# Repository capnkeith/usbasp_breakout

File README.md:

# usbasp_breakout
A breakout board to aid in connecting and disconnecting a USBASP or similar from a breadboard rapidly. Features an RJ45, 10x1 header, 5x2 header, and 3x2 header. Fits most simple ISP programmers

This is a kikad project. 

Pinouts:

10x1 header 

	1 - VCC
	2 - GND
	3 - MOSI
	4 - VCC
	5 - RESET
	6 - SCK
	7 - MISO 
	8 - GND
 
5x2 header

	1 - MISO
	2 - VCC
	3 - NC
	4 - GND
	5 - RESET
	6 - GND
	7 - SCK
	8 - GND
	9 - MISO
	10 - GND 
 
3x2 Header

	1 - MISO
	2 - VCC
	3 - SCK
	4 - MOSI
	5 - RESET
	6 - GND
 
RJ45 Connector

	1 - VCC
	2 - NC
	3 - MOSI
	4 - NC
	5 - REST
	6 - SCK
	7 - MISO
	8 - GND

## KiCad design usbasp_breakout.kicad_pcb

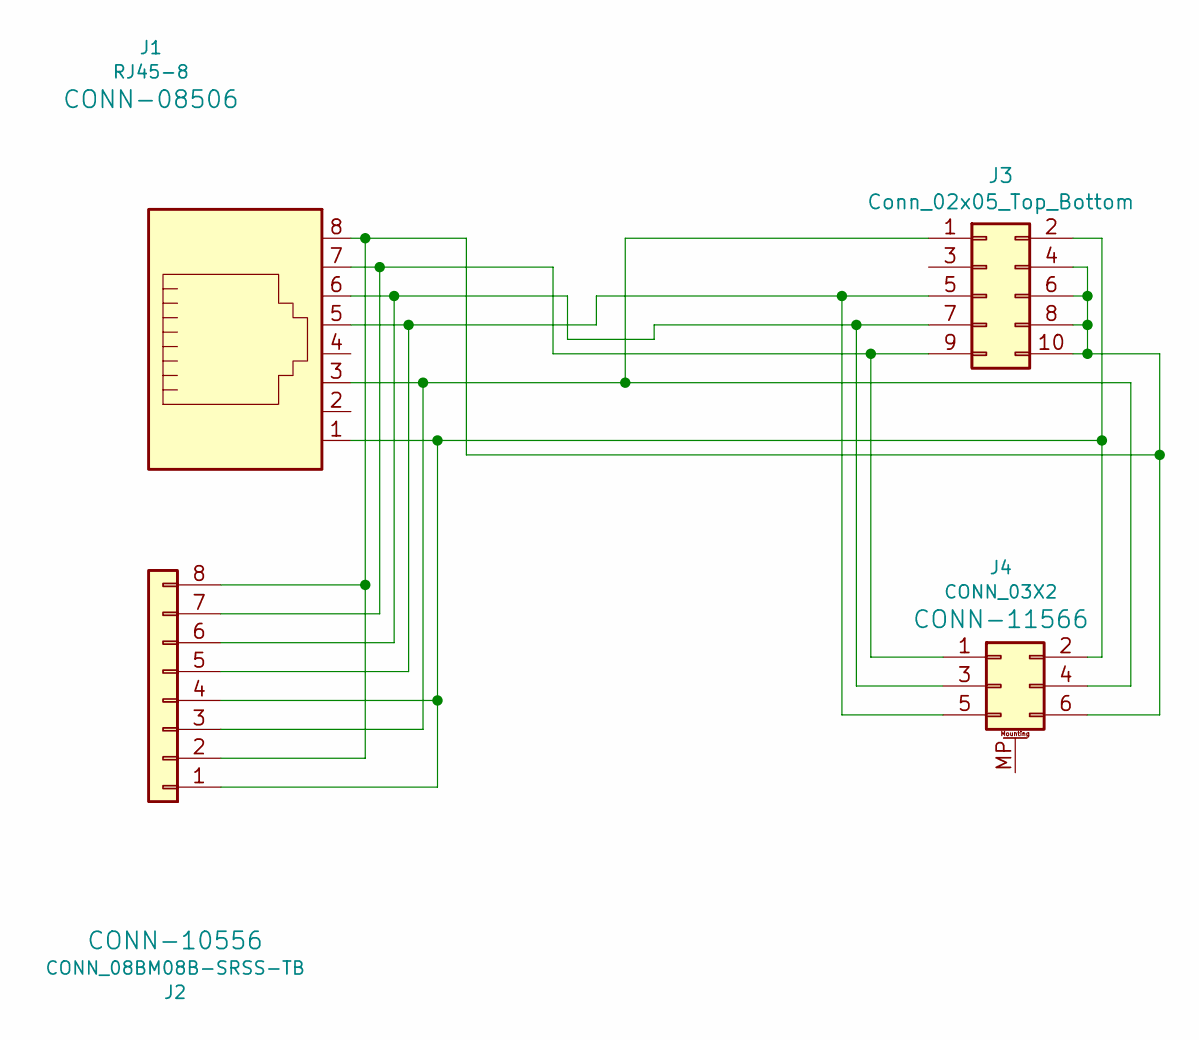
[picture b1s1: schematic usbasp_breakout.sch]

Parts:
J1: RJ45-8; RJ45_Amphenol_54602-x08_Horizontal
J2: CONN_08BM08B-SRSS-TB; PinHeader_1x08_P2.54mm_Vertical
J3: Conn_02x05_Top_Bottom; PinSocket_2x05_P2.54mm_Vertical
J4: CONN_03X2; PinSocket_2x03_P2.54mm_Vertical

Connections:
unnamed: J1.1, J2.1, J2.4, J3.2, J4.2
unnamed: J1.3, J2.3, J3.1, J4.4
unnamed: J1.5, J2.5, J3.5, J4.5
unnamed: J1.6, J2.6, J3.7, J4.3
unnamed: J1.7, J2.7, J3.9, J4.1
unnamed: J1.8, J2.2, J2.8, J3.4, J3.6, J3.8, J3.10, J4.6

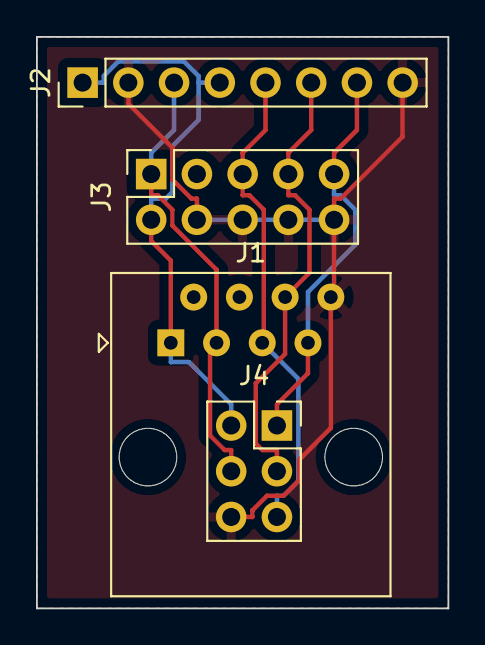
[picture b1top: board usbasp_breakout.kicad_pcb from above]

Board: 2 copper layers, 22.9 x 31.7 mm, 4 parts (0 on the bottom side), 6 nets.
